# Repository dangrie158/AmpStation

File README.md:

# Class D Amplifier Project

This project aims to repurpose an old Teufel Decoder Station Case by building a Class D amplifier inside it.

## Introduction

The old Teufel Decoder Station Case has been transformed into a powerful Class D amplifier in this project.

## Features

- Compact design that fits perfectly into the Teufel Decoder Station Case
- High-efficiency Class D amplifier technology
- Excellent audio quality with low distortion
- Multiple input options for versatile connectivity
- Built-in protection circuitry for safe operation

This project is licensed under the [MIT License](LICENSE).

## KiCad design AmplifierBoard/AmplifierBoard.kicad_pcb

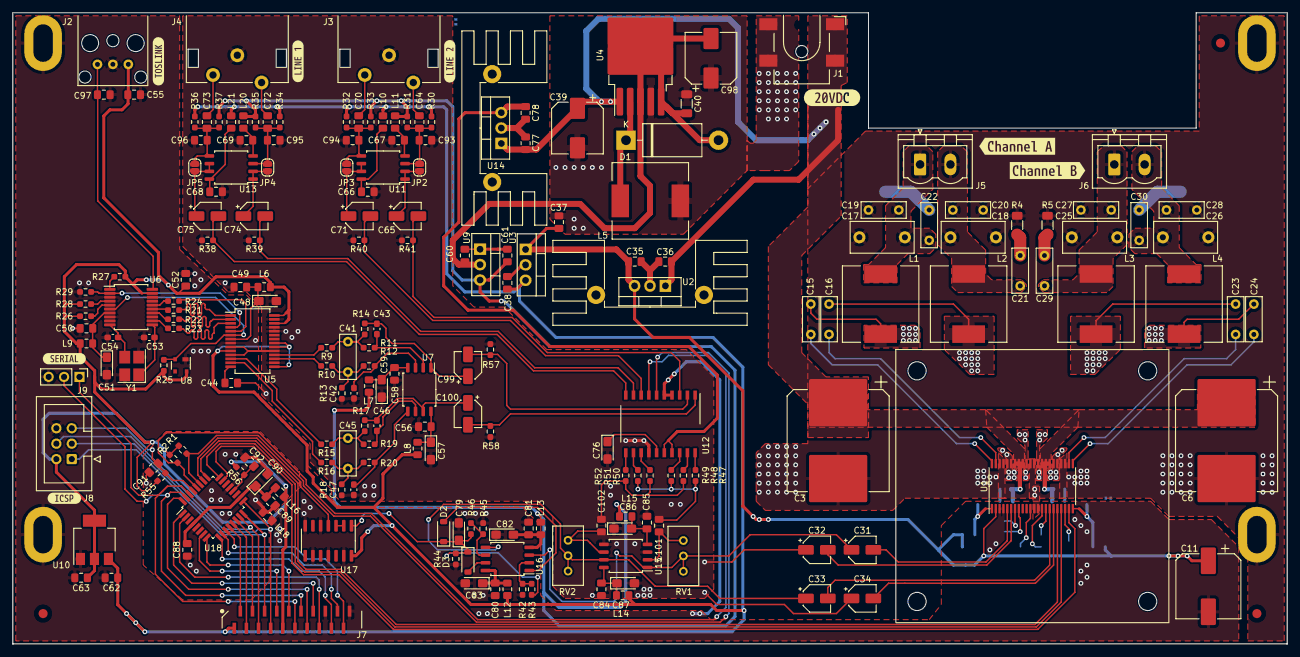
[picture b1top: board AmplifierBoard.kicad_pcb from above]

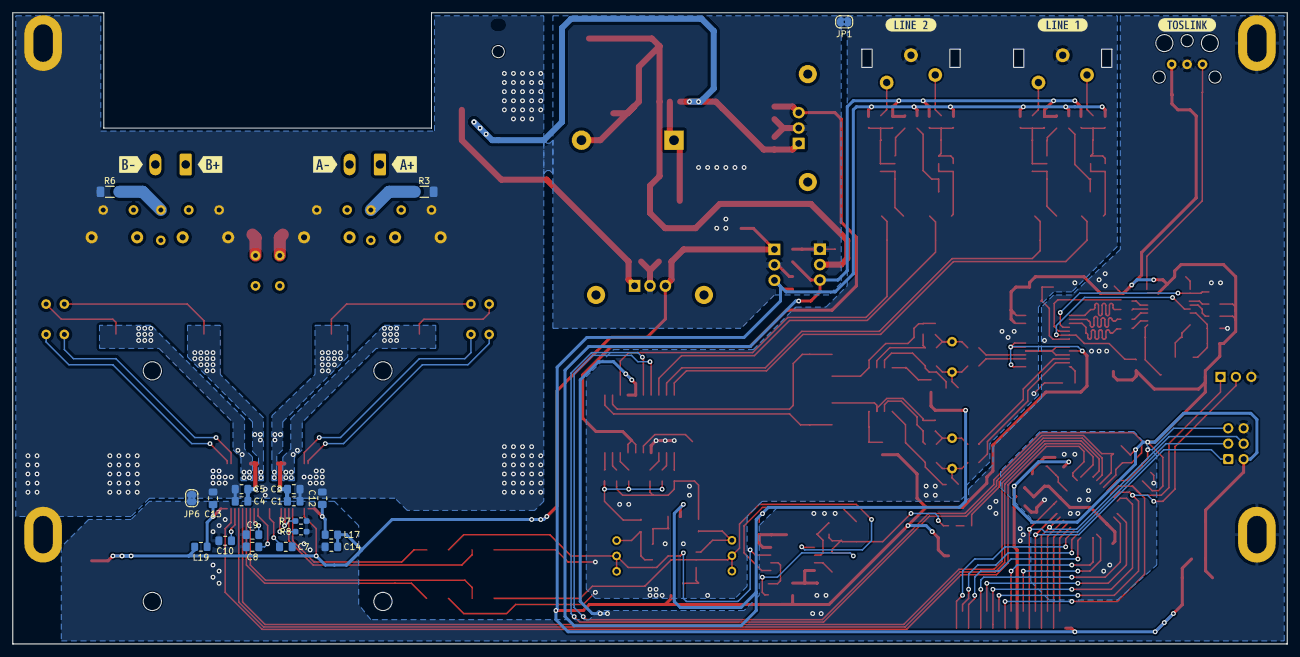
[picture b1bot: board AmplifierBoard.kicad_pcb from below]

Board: 2 copper layers, 210.0 x 104.0 mm, 243 parts (26 on the bottom side), 145 nets.

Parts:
C1, C2, C4, C5: 1µF 50V; C_0805_2012Metric_Pad1.18x1.45mm_HandSolder
C3, C6: 470µF 50V; CP_Elec_16x17.5
C7, C8: 1µF; C_0805_2012Metric_Pad1.18x1.45mm_HandSolder
C9: 10nF; C_0805_2012Metric_Pad1.18x1.45mm_HandSolder
C10, C35, C36, C37, C38, C49, C50, C52, C55, C56, C58, C60, C61, C62, C63, C64, C66, C67, C68, C69, C70, C72, C73, C77, C78, C80, C81, C84, C85, C88, C89, C91, C92: 100nF; C_0805_2012Metric_Pad1.18x1.45mm_HandSolder
C11: 470µF 16V; CP_Elec_10x10.5
C12, C13: 100n; C_0805_2012Metric_Pad1.18x1.45mm_HandSolder
C14: 100nF 16V; C_0805_2012Metric_Pad1.18x1.45mm_HandSolder
C15, C16, C23, C24: 33nF; C_Rect_L7.2mm_W2.5mm_P5.00mm_FKS2_FKP2_MKS2_MKP2
C17, C18, C25, C26: 1µ; C_Rect_L10.3mm_W5.0mm_P7.50mm_MKS4
C19, C20, C27, C28: 1n; C_Rect_L7.2mm_W2.5mm_P5.00mm_FKS2_FKP2_MKS2_MKP2
C21, C22, C29, C30: 10n; C_Rect_L7.2mm_W2.5mm_P5.00mm_FKS2_FKP2_MKS2_MKP2
C31, C32, C33, C34, C65, C71, C74, C75, C99, C100: 10µF; CP_Elec_4x5.4
C39, C98: 100µF 50V; CP_Elec_8x10
C40: 22µF; C_1206_3216Metric_Pad1.33x1.80mm_HandSolder
C41, C45: 1800pF; C_Rect_L7.2mm_W2.5mm_P5.00mm_FKS2_FKP2_MKS2_MKP2
C42, C43, C46, C47: 470pF; C_0603_1608Metric_Pad1.08x0.95mm_HandSolder
C44: 1µ; C_0805_2012Metric_Pad1.18x1.45mm_HandSolder
C48, C51, C57, C59, C76, C79, C82, C83, C86, C87, C90: 10µF; CP_EIA-3216-18_Kemet-A_Pad1.58x1.35mm_HandSolder
C53, C54: 18pF; C_0603_1608Metric_Pad1.08x0.95mm_HandSolder
C93, C94, C95, C96: 100pF; C_0805_2012Metric_Pad1.18x1.45mm_HandSolder
C97: 30pF; C_0805_2012Metric_Pad1.18x1.45mm_HandSolder
C101, C102: 10µF; C_0805_2012Metric_Pad1.18x1.45mm_HandSolder
D1: 1N5822; D_DO-201AD_P15.24mm_Horizontal
D2, D3: 1N4148; D_SOD-123
FID1, FID2, FID3: Fiducial; Fiducial_1.5mm_Mask3mm
H1, H2, H3, H4: 3.2mm Hole Oblong
HS1: Heatsink; ATS-CPX045045010-197-C1-R0
HS2, HS5: Heatsink; ASS_0871_HS
J1: 12-20V; BarrelJack_CLIFF_FC681465S_SMT_Horizontal
J2: Digital; FCR684205R
J3: AUX1; RCJ-2223
J4: AUX2; RCJ-2223
J5: CHANNEL A; PhoenixContact_MSTBVA_2,5_2-G_1x02_P5.00mm_Vertical
J6: CHANNEL B; PhoenixContact_MSTBVA_2,5_2-G_1x02_P5.00mm_Vertical
J7: Frontpanel; PCB-C-20-T-SMT
J8: ICSP; IDC-Header_2x03_P2.54mm_Vertical
J9: Serial Debug; PinHeader_1x03_P2.54mm_Vertical
JP1, JP6: Star Ground; SolderJumper-2_P1.3mm_Bridged2Bar_RoundedPad1.0x1.5mm
JP2, JP3, JP4, JP5: Bypass; SolderJumper-2_P1.3mm_Open_RoundedPad1.0x1.5mm
L1, L2, L3, L4: 10µH; L_12x12mm_H4.5mm
L5: 68µH; L_12x12mm_H4.5mm
L6, L7, L8, L9, L10, L11, L12, L13, L14, L15, L16, L17, L18, L19, L20, L21: 10µH; L_0805_2012Metric_Pad1.15x1.40mm_HandSolder
R1, R2, R55, R56: 4k7; R_0603_1608Metric_Pad0.98x0.95mm_HandSolder
R3, R4, R5, R6: 3R3; R_1206_3216Metric_Pad1.30x1.75mm_HandSolder
R7: 27k; R_0603_1608Metric_Pad0.98x0.95mm_HandSolder
R8, R25, R26, R27, R28, R29, R43, R44, R46: 10k; R_0603_1608Metric_Pad0.98x0.95mm_HandSolder
R9, R10, R15, R16: 1.8k; R_0603_1608Metric_Pad0.98x0.95mm_HandSolder
R11, R12, R19, R20: 680; R_0603_1608Metric_Pad0.98x0.95mm_HandSolder
R13, R14, R17, R18: 3k3; R_0603_1608Metric_Pad0.98x0.95mm_HandSolder
R21, R22, R23, R24: 22; R_0603_1608Metric_Pad0.98x0.95mm_HandSolder
R30, R31, R32, R33, R34, R35, R36, R37, R38, R39, R40, R41, R57, R58: 100k; R_0603_1608Metric_Pad0.98x0.95mm_HandSolder
R42, R45: 0; R_0603_1608Metric_Pad0.98x0.95mm_HandSolder
R47, R48, R49, R50, R51, R52: 1k; R_0603_1608Metric_Pad0.98x0.95mm_HandSolder
RV1, RV2: 50k; Potentiometer_Bourns_3296W_Vertical
U1: TPA3251; HTSSOP-44_6.1x14mm_P0.635mm_TopEP4.14x7.01mm
U2: L7812; TO-220-3_Vertical
U3: L7805; TO-220-3_Vertical
U4: LM2576S-12; TO-263-5_TabPin3
U5: PCM1793; SSOP-28_5.3x10.2mm_P0.65mm
U6: WM8804; SSOP-20_5.3x7.2mm_P0.65mm
U7, U11, U13, U15: LM833; SOIC-8_5.23x5.23mm_P1.27mm
U8: MIC811TUY; SOT-143
U9: L7905; TO-220-3_Vertical
U10: LM1117MP-3.3; SOT-223-3_TabPin2
U12: PT2258; SO-20_12.8x7.5mm_P1.27mm
U14: L7809; TO-220-3_Vertical
U16: LM358; SOIC-8_5.23x5.23mm_P1.27mm
U17: 74HC14; SOIC-14_3.9x8.7mm_P1.27mm
U18: ATmega328PB-A; TQFP-32_7x7mm_P0.8mm
Y1: 12MHz; Crystal_SMD_3225-4Pin_3.2x2.5mm_HandSoldering
kibuzzard-65BCF8D4: G***; kibuzzard-65BCF8D4
kibuzzard-65BCF90F: G***; kibuzzard-65BCF90F
kibuzzard-65BCFB63: G***; kibuzzard-65BCFB63
kibuzzard-65BCFB77: G***; kibuzzard-65BCFB77
kibuzzard-65BCFB90: G***; kibuzzard-65BCFB90
kibuzzard-65BCFBA1: G***; kibuzzard-65BCFBA1
kibuzzard-65BD00A1: G***; kibuzzard-65BD00A1
kibuzzard-65BD00A6: G***; kibuzzard-65BD00A6
kibuzzard-65BD000D: G***; kibuzzard-65BD000D
kibuzzard-65BD0ED3: G***; kibuzzard-65BD0ED3
kibuzzard-65BD00F0: G***; kibuzzard-65BD00F0
kibuzzard-65BD0F18: G***; kibuzzard-65BD0F18
kibuzzard-65BD008D: G***; kibuzzard-65BD008D
kibuzzard-65BD0105: G***; kibuzzard-65BD0105
kibuzzard-65BD0157: G***; kibuzzard-65BD0157

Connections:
+3V3: C52.1, C55.1, C63.1, J2.3 (VCC), J7.9, J8.2, L6.1, L9.1, L16.1, R1.1, R2.1, R25.1, R26.1, R27.1, R28.1, R55.2, R56.2, U5.26 (FMT0), U5.28 (FMT2), U6.19 (DVDD), U8.4 (VCC), U10.2 (VO)
+5V: C38.1, C62.1, J7.1, L8.1, L10.1, L12.1, L14.1, L21.1, R30.1, R32.1, R34.1, R36.1, U3.3 (OUT), U5.10 (VCCR), U5.15 (VCCC), U5.20 (VCCL), U5.21 (VCCF), U10.3 (VI), U17.14 (VCC)
+9V: C78.1, U12.16 (VCC), U12.17 (CODE1), U14.3 (OUT)
+12V: C11.1, C14.1, C35.1, C37.1, L17.1, L19.1, U1.2 (VDD), U2.3 (OUT), U3.1 (IN)
-5V: C61.2, L7.2, L11.2, L13.2, L15.2, L20.2, R31.2, R33.2, R35.2, R37.2, U9.3 (VO)
-12V: C40.2, C60.2, C98.2, D1.2 (A), U4.3 (GND), U4.5 (~ON/OFF), U9.2 (VI)
/AnalogBuffers/IN1: C64.1, J3.3 (IN1)
/AnalogBuffers/IN2: C70.1, J3.2 (IN2)
/AnalogBuffers/IN3: C72.1, J4.3 (IN1)
/AnalogBuffers/IN4: C73.1, J4.2 (IN2)
/AnalogBuffers/OUT1: C65.2, R41.1, U12.3 (IN3)
/AnalogBuffers/OUT2: C71.2, R40.1, U12.8 (IN4)
/AnalogBuffers/OUT3: C74.2, R39.1, U12.9 (IN5)
/AnalogBuffers/OUT4: C75.2, R38.1, U12.10 (IN6)
/MCU/MCUGND: C88.2, C89.2, C90.2, C91.1, C92.1, L18.1, U18.5 (GND), U18.21 (GND)
/MCU/MISO: J7.6, J8.1, U18.16 (PB4)
/MCU/MOSI: J7.5, J8.4, U18.15 (PB3)
/MCU/RXD: J7.11, J9.1, U18.30 (PD0)
/MCU/SCK: J7.7, J8.3, U18.17 (PB5)
/MCU/TXD: J7.12, J9.2, U18.31 (PD1)
/MCU/~RESET: C91.2, J8.5, R55.1, U18.29 (~RESET/PC6)
/PowerAmp/SPKA+: C17.1, C19.1, C22.1, J5.1, L1.2
/PowerAmp/SPKA-: C18.2, C20.2, C21.2, J5.2, L2.2
/PowerAmp/SPKB+: C25.1, C27.1, C29.1, J6.1, L3.2
/PowerAmp/SPKB-: C26.2, C28.2, C30.2, J6.2, L4.2
/TosLink DAC/ERR: R29.2, U5.4 (MUTE), U6.2 (GP0/SWIFM)
/TosLink DAC/LOUT: C99.2, R57.1, U12.2 (IN2)
/TosLink DAC/ROUT: C100.2, R58.1, U12.1 (IN1)
/TosLink DAC/RX: C97.1, J2.1 (Data), U6.20 (RX0)
/TosLink DAC/~RST: R25.2, U5.6 (~RST), U6.6 (RESETB), U8.2 (~RESET)
AMP_CLIP: U1.21 (~CLIP_OTW), U18.23 (PC0)
AMP_FAULT: U1.19 (~FAULT), U18.24 (PC1)
AMP_PWR: U1.18 (~RESET), U18.25 (PC2)
AUDIO_DETECT: U17.4, U18.26 (PC3)
GND: C1.2, C2.2, C3.2, C4.2, C5.2, C6.2, C12.2, C13.2, C17.2, C18.1, C19.2, C20.1, C25.2, C26.1, C27.2, C28.1, C35.2, C36.2, C37.2, C38.2, C39.2, C40.1, C60.1, C61.1, C77.2, C78.2, C98.1, H2.1, H4.1, J1.2, J1.3, JP1.1 (A), JP6.1 (A), L5.2, R3.1, R4.1, R5.1, R6.1, U1.12 (GND), U1.13 (GND), U1.25 (GND), U1.26 (GND), U1.33 (GND), U1.34 (GND), U1.41 (GND), U1.42 (GND), U2.2 (GND), U3.2 (GND), U4.4 (FB), U9.1 (GND), U14.2 (GND)
GNDA: C32.1, C34.1, C42.2, C44.2, C47.2, C48.2, C49.2, C56.2, C57.2, C58.2, C59.1, C66.2, C67.2, C68.2, C69.2, C76.2, C84.2, C85.2, C86.1, C87.2, C93.1, C94.1, C95.1, C96.1, J3.1 (EXT), J4.1 (EXT), JP1.2 (B), R13.2, R18.2, R38.2, R39.2, R40.2, R41.2, R57.2, R58.2, U5.9 (AGNDF), U5.11 (AGNDR), U5.16 (AGNDC), U5.19 (AGNDL), U5.24 (DEMP0), U5.25 (DEMP1), U5.27 (FMT1), U12.14 (AGND), U15.3 (+), U15.5 (+)
GNDD: C7.2, C8.2, C9.2, C10.2, C11.2, C14.2, C50.2, C51.2, C52.2, C53.2, C54.2, C55.2, C62.2, C63.2, C79.2, C80.2, C81.2, C82.1, C83.2, C97.2, H1.1, H3.1, J2.2 (GND), J7.16, J7.20, J8.6, J9.3, JP6.2 (B), L18.2, R7.1, R8.1, R29.1, R42.1, R44.1, R45.1, U1.3 (M1), U1.4 (M2), U5.8 (DGND), U6.3 (SDIN/HWM), U6.8 (PGND), U6.18 (DGND), U8.1 (GND), U10.1 (GND), U12.4 (CODE2), U12.5 (DGND), U17.5, U17.7 (GND), U17.9, U17.11, U17.13, Y1.2, Y1.4
MIX_A: C31.1, RV1.1, RV1.2, U15.1, U16.3 (+)
MIX_B: C33.1, RV2.1, RV2.2, U15.7, U16.5 (+)
unnamed: C15.1, L1.1, U1.39 (OUT_A), U1.40 (OUT_A)
unnamed: C21.1, R4.2
unnamed: C22.2, R3.2
unnamed: C24.1, L4.1, U1.27 (OUT_D), U1.28 (OUT_D)
unnamed: C29.2, R5.2
unnamed: C30.1, R6.2
unnamed: C41.1, R9.1, R11.2, R14.2
unnamed: C41.2, R10.1, R12.2, R13.1
unnamed: C43.1, C99.1, R14.1, U7.1
unnamed: C45.1, R15.1, R17.2, R19.2
unnamed: C45.2, R16.1, R18.1, R20.2
unnamed: C46.1, C100.1, R17.1, U7.7
unnamed: C101.1, R47.2, R49.2, R51.2
unnamed: C102.1, R48.2, R50.2, R52.2
unnamed: D1.1 (K), L5.1, U4.2 (OUT)
unnamed: D2.2 (A), U16.1
unnamed: C79.1, D2.1 (K), D3.1 (K), R43.2, R44.2, R46.2, U17.1
unnamed: D3.2 (A), U16.7
unnamed: J7.2, U18.12 (PB0)
unnamed: J7.3, U18.13 (PB1)
unnamed: J7.4, U18.14 (PB2)
unnamed: J7.8, U18.7 (XTAL1/PB6)
unnamed: J7.10, U18.8 (XTAL2/PB7)
unnamed: J7.13, U18.32 (PD2)
unnamed: J7.14, U18.1 (PD3)
unnamed: J7.15, U18.2 (PD4)
unnamed: J7.17, U18.9 (PD5)
unnamed: J7.18, U18.10 (PD6)
unnamed: J7.19, U18.11 (PD7)
unnamed: C64.2, C93.2, JP2.1 (A), R30.2, R31.1, U11.3 (+)
unnamed: C65.1, JP2.2 (B), U11.1, U11.2 (-)
unnamed: C70.2, C94.2, JP3.1 (A), R32.2, R33.1, U11.5 (+)
unnamed: C71.1, JP3.2 (B), U11.6 (-), U11.7
unnamed: C72.2, C95.2, JP4.1 (A), R34.2, R35.1, U13.3 (+)
unnamed: C74.1, JP4.2 (B), U13.1, U13.2 (-)
unnamed: C73.2, C96.2, JP5.1 (A), R36.2, R37.1, U13.5 (+)
unnamed: C75.1, JP5.2 (B), U13.6 (-), U13.7
unnamed: C8.1, U1.14 (AVDD)
unnamed: C15.2, U1.44 (BST_A)
unnamed: C16.2, U1.43 (BST_B)
unnamed: C9.1, U1.15 (C_START)
unnamed: C7.1, U1.11 (DVDD)
unnamed: R8.2, U1.8 (FREQ_ADJ)
unnamed: C12.1, L17.2, U1.1 (GVDD_AB)
unnamed: C31.2, U1.5 (INPUT_A)
unnamed: C32.2, U1.6 (INPUT_B)
unnamed: R7.2, U1.7 (OC_ADJ)
unnamed: C16.1, L2.1, U1.35 (OUT_B)
unnamed: C10.1, U1.20 (VBG)
unnamed: C23.2, U1.24 (BST_C)
unnamed: C24.2, U1.23 (BST_D)
unnamed: C13.1, L19.2, U1.22 (GVDD_CD)
unnamed: C33.2, U1.16 (INPUT_C)
unnamed: C34.2, U1.17 (INPUT_D)
unnamed: C23.1, L3.1, U1.32 (OUT_C)
unnamed: R22.1, U5.2 (BCK)
unnamed: R23.1, U5.3 (DATA)
unnamed: R21.1, U5.1 (LRCK)
unnamed: R24.1, U5.5 (SCK)
unnamed: C44.1, U5.14 (VCOM)
unnamed: C48.1, C49.1, L6.2, U5.7 (VDD)
unnamed: R10.2, U5.17 (VOUTL+)
unnamed: R9.2, U5.18 (VOUTL-)
unnamed: R16.2, U5.13 (VOUTR+)
unnamed: R15.2, U5.12 (VOUTR-)
unnamed: R22.2, U6.14 (BCLK)
unnamed: R26.2, U6.5 (CSB/GP1)
unnamed: R23.2, U6.12 (DOUT)
unnamed: R21.2, U6.15 (LRCK)
unnamed: R24.2, U6.16 (MCLK)
unnamed: C50.1, C51.1, L9.2, U6.7 (PVDD)
unnamed: R27.2, U6.1 (SCLK)
unnamed: R28.2, U6.4 (SDOUT/GP2)
unnamed: C53.1, U6.11 (XIN), Y1.1
unnamed: C54.1, U6.10 (XOP), Y1.3
unnamed: C42.1, R12.1, U7.3 (+)
unnamed: C43.2, R11.1, U7.2 (-)
unnamed: C47.1, R20.1, U7.5 (+)
unnamed: C46.2, R19.1, U7.6 (-)
unnamed: C56.1, C57.1, L8.2, U7.8 (V+)
unnamed: C58.1, C59.2, L7.1, U7.4 (V-)
unnamed: C66.1, L10.2, U11.8 (V+)
unnamed: C67.1, L11.1, U11.4 (V-)
unnamed: R47.1, U12.20 (OUT1)
unnamed: R48.1, U12.19 (OUT2)
unnamed: R49.1, U12.18 (OUT3)
unnamed: R50.1, U12.13 (OUT4)
unnamed: R51.1, U12.12 (OUT5)
unnamed: R52.1, U12.11 (OUT6)
unnamed: C76.1, U12.15 (REF)
unnamed: C68.1, L21.2, U13.8 (V+)
unnamed: C69.1, L20.1, U13.4 (V-)
unnamed: C101.2, RV1.3, U15.2 (-)
unnamed: C102.2, RV2.3, U15.6 (-)
unnamed: C84.1, C87.1, L14.2, U15.8 (V+)
unnamed: C85.1, C86.2, L15.1, U15.4 (V-)
unnamed: R42.2, R43.1, U16.2 (-)
unnamed: R45.2, R46.1, U16.6 (-)
unnamed: C80.1, C83.1, L12.2, U16.8 (V+)
unnamed: C81.1, C82.2, L13.1, U16.4 (V-)
unnamed: U17.2, U17.3
unnamed: C92.2, R56.1, U18.20 (AREF)
unnamed: C88.1, C89.1, C90.1, L16.2, U18.4 (VCC), U18.18 (AVCC)
SCL: R1.2, U12.6 (SCL), U18.27 (PC4)
SDA: R2.2, U12.7 (SDA), U18.28 (PC5)
VDC: C1.1, C2.1, C3.1, C4.1, C5.1, C6.1, C36.1, C39.1, C77.1, J1.1, U1.29 (PVDD_CD), U1.30 (PVDD_CD), U1.31 (PVDD_CD), U1.36 (PVDD_AB), U1.37 (PVDD_AB), U1.38 (PVDD_AB), U2.1 (IN), U4.1 (VIN), U14.1 (IN)

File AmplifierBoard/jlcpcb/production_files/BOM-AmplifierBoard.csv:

Comment,Designator,Footprint,LCSC
10µH,"L10,L11,L12,L13,L14,L15,L16,L17,L18,L19,L20,L21,L6,L7,L8,L9",L_0805_2012Metric_Pad1.15x1.40mm_HandSolder,C1046
30pF,C97,C_0805_2012Metric_Pad1.18x1.45mm_HandSolder,C107114
22µF,C40,C_1206_3216Metric_Pad1.33x1.80mm_HandSolder,C12891
470pF,"C42,C43,C46,C47",C_0603_1608Metric_Pad1.08x0.95mm_HandSolder,C1620
18pF,"C53,C54",C_0603_1608Metric_Pad1.08x0.95mm_HandSolder,C1647
33nF,"C15,C16",C_Rect_L7.2mm_W2.5mm_P5.00mm_FKS2_FKP2_MKS2_MKP2,C1739
100pF,"C93,C94,C95,C96",C_0805_2012Metric_Pad1.18x1.45mm_HandSolder,C1790
0,"R43,R46",R_0603_1608Metric_Pad0.98x0.95mm_HandSolder,C21189
1k,"R47,R48,R49,R50,R51,R52",R_0603_1608Metric_Pad0.98x0.95mm_HandSolder,C21190
3k3,"R13,R14,R17,R18",R_0603_1608Metric_Pad0.98x0.95mm_HandSolder,C22978
4k7,"R1,R2,R55,R56",R_0603_1608Metric_Pad0.98x0.95mm_HandSolder,C23162
680,"R11,R12,R19,R20",R_0603_1608Metric_Pad0.98x0.95mm_HandSolder,C23228
22,"R21,R22,R23,R24",R_0603_1608Metric_Pad0.98x0.95mm_HandSolder,C23345
100k,"R30,R31,R32,R33,R34,R35,R36,R37,R38,R39,R40,R41,R57,R58",R_0603_1608Metric_Pad0.98x0.95mm_HandSolder,C25803
10k,"R25,R26,R27,R28,R29,R42,R44,R45,R53,R54,R8",R_0603_1608Metric_Pad0.98x0.95mm_HandSolder,C25804
100nF,"C10,C12,C13,C14,C35,C36,C37,C38,C49,C50,C52,C55,C56,C58,C60,C61,C62,C63,C64,C66,C67,C68,C69,C70,C72,C73,C77,C78,C80,C81,C84,C85,C88,C89,C91,C92",C_0805_2012Metric_Pad1.18x1.45mm_HandSolder,C28233
1µF 50V,"C1,C2,C4,C44,C5,C7,C8",C_0805_2012Metric_Pad1.18x1.45mm_HandSolder,C28323
22k,R7,R_0603_1608Metric_Pad0.98x0.95mm_HandSolder,C31850
1.8k,"R10,R15,R16,R9",R_0603_1608Metric_Pad0.98x0.95mm_HandSolder,C4177
74HC14,U17,SOIC-14_3.9x8.7mm_P1.27mm,C5605
10µF,C83,CP_EIA-3216-18_Kemet-A_Pad1.58x1.35mm_HandSolder,C7171
LM358,U16,SOIC-8_5.23x5.23mm_P1.27mm,C7950
1N4148,"D2,D3",D_SOD-123,C81598
12MHz,Y1,Crystal_SMD_3225-4Pin_3.2x2.5mm_HandSoldering,C9002
~,H2,3.2mm Hole Oblong,
~,H1,3.2mm Hole Oblong,
~,H4,3.2mm Hole Oblong,
~,H3,3.2mm Hole Oblong,
1µ,C26,C_Rect_L10.3mm_W5.0mm_P7.50mm_MKS4,
AUX1,J3,RCJ-2223,
1µ,C25,C_Rect_L10.3mm_W5.0mm_P7.50mm_MKS4,
10n,C29,C_Rect_L7.2mm_W2.5mm_P5.00mm_FKS2_FKP2_MKS2_MKP2,
LM1117MP-3.3,U10,SOT-223-3_TabPin2,
LM833,U11,SOIC-8_5.23x5.23mm_P1.27mm,
Heatsink,HS5,ASS_0871_HS,
1n,C27,C_Rect_L7.2mm_W2.5mm_P5.00mm_FKS2_FKP2_MKS2_MKP2,
10µH,L4,L_12x12mm_H4.5mm,
12-20V,J1,BarrelJack_CLIFF_FC681465S_SMT_Horizontal,
10µF,C31,CP_Elec_4x5.4,
1N5822,D1,D_DO-201AD_P15.24mm_Horizontal,
Bypass,JP3,SolderJumper-2_P1.3mm_Open_RoundedPad1.0x1.5mm,
1n,C20,C_Rect_L7.2mm_W2.5mm_P5.00mm_FKS2_FKP2_MKS2_MKP2,
33nF,C24,C_Rect_L7.2mm_W2.5mm_P5.00mm_FKS2_FKP2_MKS2_MKP2,
Digital,J2,FCR684205R,
Heatsink,HS1,ATS-CPX045045010-197-C1-R0,
AUX2,J4,RCJ-2223,
MIC811TUY,U8,SOT-143,
1n,C19,C_Rect_L7.2mm_W2.5mm_P5.00mm_FKS2_FKP2_MKS2_MKP2,
L7809,U14,TO-220-3_Vertical,
10µF,C32,CP_Elec_4x5.4,
50k,RV2,Potentiometer_Bourns_3296W_Vertical,
10n,C22,C_Rect_L7.2mm_W2.5mm_P5.00mm_FKS2_FKP2_MKS2_MKP2,
PCM1793,U5,SSOP-28_5.3x10.2mm_P0.65mm,
Fiducial,FID3,Fiducial_1.5mm_Mask3mm,
CHANNEL A,J5,"PhoenixContact_MSTBVA_2,5_2-G_1x02_P5.00mm_Vertical",
WM8804,U6,SSOP-20_5.3x7.2mm_P0.65mm,
10µF,C76,CP_EIA-3216-18_Kemet-A_Pad1.58x1.35mm_HandSolder,
10µF,C59,CP_EIA-3216-18_Kemet-A_Pad1.58x1.35mm_HandSolder,
50k,RV1,Potentiometer_Bourns_3296W_Vertical,
10µF,C57,CP_EIA-3216-18_Kemet-A_Pad1.58x1.35mm_HandSolder,
3R3,R5,R_1206_3216Metric_Pad1.30x1.75mm_HandSolder,
10µF,C90,CP_EIA-3216-18_Kemet-A_Pad1.58x1.35mm_HandSolder,
Fiducial,FID1,Fiducial_1.5mm_Mask3mm,
10µF,C75,CP_Elec_4x5.4,
Bypass,JP2,SolderJumper-2_P1.3mm_Open_RoundedPad1.0x1.5mm,
10n,C21,C_Rect_L7.2mm_W2.5mm_P5.00mm_FKS2_FKP2_MKS2_MKP2,
L7805,U3,TO-220-3_Vertical,
10µF,C86,CP_EIA-3216-18_Kemet-A_Pad1.58x1.35mm_HandSolder,
PT2258,U12,SO-20_12.8x7.5mm_P1.27mm,
10µF,C99,CP_Elec_4x5.4,
3R3,R4,R_1206_3216Metric_Pad1.30x1.75mm_HandSolder,
Bypass,JP5,SolderJumper-2_P1.3mm_Open_RoundedPad1.0x1.5mm,
10µH,L2,L_12x12mm_H4.5mm,
L7812,U2,TO-220-3_Vertical,
1800pF,C45,C_Rect_L7.2mm_W2.5mm_P5.00mm_FKS2_FKP2_MKS2_MKP2,
10µF,C87,CP_EIA-3216-18_Kemet-A_Pad1.58x1.35mm_HandSolder,
10µF,C48,CP_EIA-3216-18_Kemet-A_Pad1.58x1.35mm_HandSolder,
1µ,C17,C_Rect_L10.3mm_W5.0mm_P7.50mm_MKS4,
Fiducial,FID2,Fiducial_1.5mm_Mask3mm,
Serial Debug,J9,PinHeader_1x03_P2.54mm_Vertical,
10µF,C51,CP_EIA-3216-18_Kemet-A_Pad1.58x1.35mm_HandSolder,
470µF 50V,C6,CP_Elec_16x17.5,
10µF,C100,CP_Elec_4x5.4,
LM2576S-12,U4,TO-263-5_TabPin3,
10µF,C34,CP_Elec_4x5.4,
Bypass,JP4,SolderJumper-2_P1.3mm_Open_RoundedPad1.0x1.5mm,
1µ,C18,C_Rect_L10.3mm_W5.0mm_P7.50mm_MKS4,
Frontpanel,J7,PCB-C-20-T-SMT,
10µF,C71,CP_Elec_4x5.4,
Heatsink,HS2,ASS_0871_HS,
LM833,U13,SOIC-8_5.23x5.23mm_P1.27mm,
LM833,U7,SOIC-8_5.23x5.23mm_P1.27mm,
100µF 50V,C39,CP_Elec_8x10,
33nF,C23,C_Rect_L7.2mm_W2.5mm_P5.00mm_FKS2_FKP2_MKS2_MKP2,
470µF 16V,C11,CP_Elec_10x10.5,
10µF,C33,CP_Elec_4x5.4,
1n,C28,C_Rect_L7.2mm_W2.5mm_P5.00mm_FKS2_FKP2_MKS2_MKP2,
10µF,C65,CP_Elec_4x5.4,
1800pF,C41,C_Rect_L7.2mm_W2.5mm_P5.00mm_FKS2_FKP2_MKS2_MKP2,
CHANNEL B,J6,"PhoenixContact_MSTBVA_2,5_2-G_1x02_P5.00mm_Vertical",
ICSP,J8,IDC-Header_2x03_P2.54mm_Vertical,
68µH,L5,L_12x12mm_H4.5mm,
L7905,U9,TO-220-3_Vertical,
10n,C30,C_Rect_L7.2mm_W2.5mm_P5.00mm_FKS2_FKP2_MKS2_MKP2,
10µF,C74,CP_Elec_4x5.4,
470µF 50V,C3,CP_Elec_16x17.5,
10µF,C82,CP_EIA-3216-18_Kemet-A_Pad1.58x1.35mm_HandSolder,
ATmega328PB-A,U18,TQFP-32_7x7mm_P0.8mm,
10µH,L1,L_12x12mm_H4.5mm,
10µH,L3,L_12x12mm_H4.5mm,
LM833,U15,SOIC-8_5.23x5.23mm_P1.27mm,
100µF 50V,C98,CP_Elec_8x10,
TPA3251,U1,HTSSOP-44_6.1x14mm_P0.635mm_TopEP4.14x7.01mm,
10µF,C79,CP_EIA-3216-18_Kemet-A_Pad1.58x1.35mm_HandSolder,
Star Ground,JP6,SolderJumper-2_P1.3mm_Bridged2Bar_RoundedPad1.0x1.5mm,
Star Ground,JP1,SolderJumper-2_P1.3mm_Bridged2Bar_RoundedPad1.0x1.5mm,
3R3,R6,R_1206_3216Metric_Pad1.30x1.75mm_HandSolder,
3R3,R3,R_1206_3216Metric_Pad1.30x1.75mm_HandSolder,
10nF,C9,C_0805_2012Metric_Pad1.18x1.45mm_HandSolder,

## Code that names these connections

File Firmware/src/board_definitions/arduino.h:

#pragma once

#include "lib/IO.h"
#include "lib/AdvancedIO.h"
#include "lib/I2C.h"

auto rs = IO::Output(IO::Port::PortB, 0);
auto rw = IO::Output(IO::Port::PortB, 1);
auto en = IO::Output(IO::Port::PortB, 2);
auto d4 = IO::Output(IO::Port::PortD, 4);
auto d5 = IO::Output(IO::Port::PortD, 5);
auto d6 = IO::Output(IO::Port::PortD, 6);
auto d7 = IO::Output(IO::Port::PortD, 7);
const auto lcd_backlight = IO::Output(IO::Port::PortB, 5);

const auto ringlight_bright = IO::Output(IO::Port::PortC, 4);
const auto ringlight_dimmed = IO::Output(IO::Port::PortC, 4);
const auto amp_power = IO::Output(IO::Port::PortC, 2);
const auto audio_detect = IO::PinChangeInterruptPin(IO::PinChangeInterruptPort::PortC, 0, IO::PullupMode::Disable);
const auto ir_receiver_pin = IO::PinChangeInterruptPin(IO::PinChangeInterruptPort::PortD, 0, IO::PullupMode::Disable);

auto enc_a = IO::PinChangeInterruptPin(IO::PinChangeInterruptPort::PortC, 4, IO::PullupMode::Enable);
auto enc_b = IO::PinChangeInterruptPin(IO::PinChangeInterruptPort::PortC, 3, IO::PullupMode::Enable);
auto enc_button_pin = IO::PinChangeInterruptPin(IO::PinChangeInterruptPort::PortC, 5, IO::PullupMode::Enable);

auto mute_pin = IO::PinChangeInterruptPin(IO::PinChangeInterruptPort::PortC, 2, IO::PullupMode::Enable);
auto amp_fault_pin = IO::PinChangeInterruptPin(IO::PinChangeInterruptPort::PortC, 1, IO::PullupMode::Enable);
auto amp_clip_pin = IO::PinChangeInterruptPin(IO::PinChangeInterruptPort::PortC, 1, IO::PullupMode::Enable);

const I2C::Master &i2c_bus = I2C::HardwareMaster::the;

constexpr uint8_t encoder_stepsize = 2;
constexpr uint16_t standby_delay_seconds = 30;
constexpr uint16_t lightsout_delay_seconds = 5;

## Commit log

2024-02-09 initial commit with current state
2024-02-10 more IO drivers for the Firmware
2024-02-10 implement step size handling for rotary encoder driver
2024-02-12 add PT2257 driver and proper interrupt driven duttons
2024-02-27 firmware with most functions and real pin definitions
2024-02-28 firmware revision for real hardware
2024-03-04 updated schematic of amplifier board
2024-03-04 move to soft i2c implementation due to wiring mshap
2024-03-04 consistent naming style in LiquidCrystal
2024-03-09 add master mix functionality to PT2258 driver
2024-03-09 fixe standby reset logic on audio detect
2024-12-23 update pcb version
2024-12-23 fix i2c driver
2024-12-24 add IR receiver functionality
2024-12-24 add atmega328p datasheet
